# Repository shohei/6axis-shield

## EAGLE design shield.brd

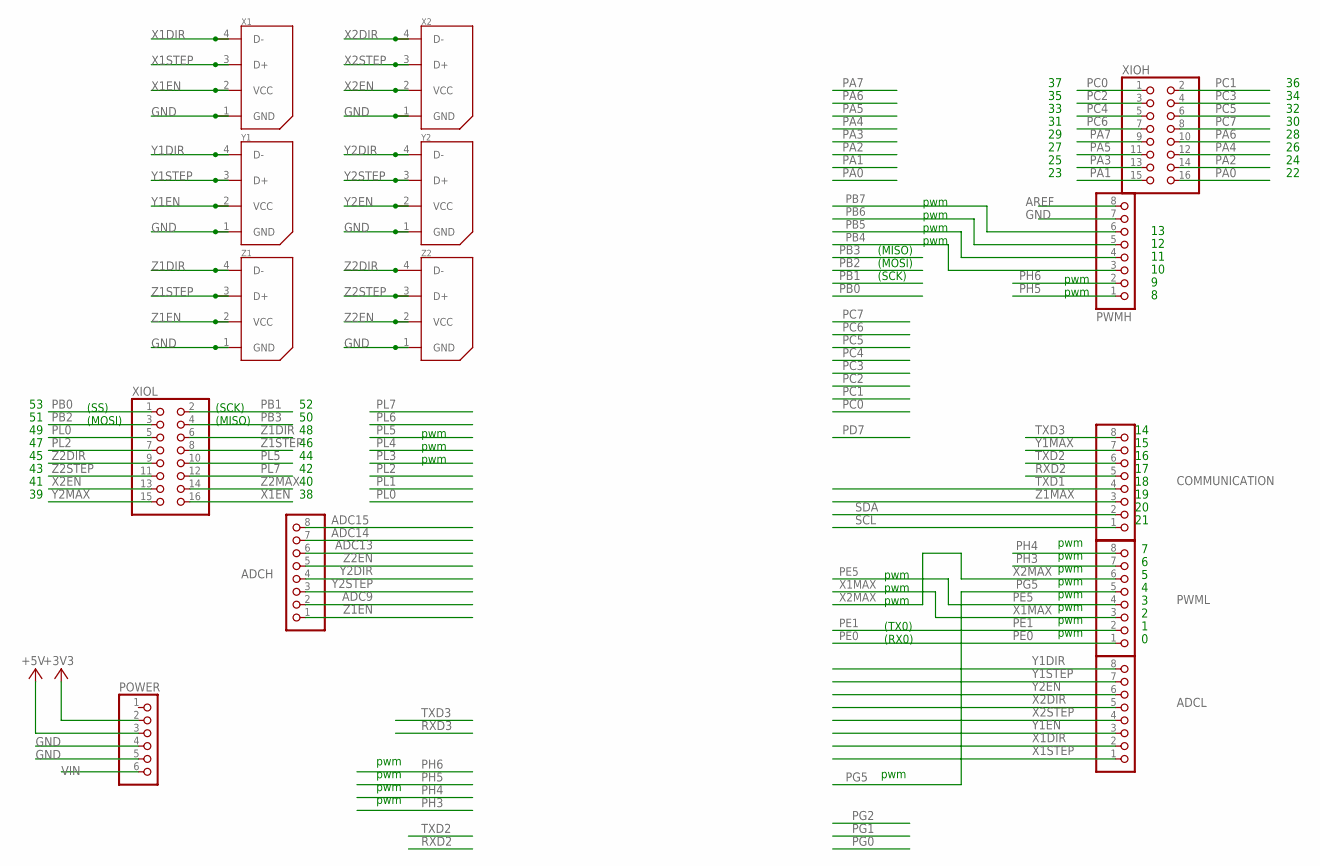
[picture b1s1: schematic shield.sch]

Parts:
ADCH: PINHD-1X8; 1X08
ADCL: PINHD-1X8; 1X08
COMMUNICATION: PINHD-1X8; 1X08
POWER: PINHD-1X6; 1X06
PWMH: PINHD-1X8; 1X08
PWML: PINHD-1X8; 1X08
X1, X2: 22-03-5045; 5267-4
XIOH: PINHD-2X8; 2X08
XIOL: PINHD-2X8; 2X08
Y1, Y2: 22-03-5045; 5267-4
Z1, Z2: 22-03-5045; 5267-4

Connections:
+3V3: POWER.2
+5V: POWER.3
ADC9: ADCH.2
ADC13: ADCH.6
ADC14: ADCH.7
ADC15: ADCH.8
AREF: PWMH.8
GND: POWER.4, POWER.5, PWMH.7, X1.1 (GND), X2.1 (GND), Y1.1 (GND), Y2.1 (GND), Z1.1 (GND), Z2.1 (GND)
PA0: XIOH.16
PA1: XIOH.15
PA2: XIOH.14
PA3: XIOH.13
PA4: XIOH.12
PA5: XIOH.11
PA6: XIOH.10
PA7: XIOH.9
PB0: XIOL.1
PB1: XIOL.2
PB2: XIOL.3
PB3: XIOL.4
PB4: PWMH.3
PB5: PWMH.4
PB6: PWMH.5
PB7: PWMH.6
PC0: XIOH.1
PC1: XIOH.2
PC2: XIOH.3
PC3: XIOH.4
PC4: XIOH.5
PC5: XIOH.6
PC6: XIOH.7
PC7: XIOH.8
PE0: PWML.1
PE1: PWML.2
PE5: PWML.4
PG5: PWML.5
PH3: PWML.7
PH4: PWML.8
PH5: PWMH.1
PH6: PWMH.2
PL0: XIOL.5
PL2: XIOL.7
PL5: XIOL.10
PL7: XIOL.12
RXD2: COMMUNICATION.5
SCL: COMMUNICATION.1
SDA: COMMUNICATION.2
TXD1: COMMUNICATION.4
TXD2: COMMUNICATION.6
TXD3: COMMUNICATION.8
VIN: POWER.6
X1DIR: ADCL.2, X1.4 (D-)
X1EN: X1.2 (VCC), XIOL.16
X1MAX: PWML.3
X1STEP: ADCL.1, X1.3 (D+)
X2DIR: ADCL.5, X2.4 (D-)
X2EN: X2.2 (VCC), XIOL.13
X2MAX: PWML.6
X2STEP: ADCL.4, X2.3 (D+)
Y1DIR: ADCL.8, Y1.4 (D-)
Y1EN: ADCL.3, Y1.2 (VCC)
Y1MAX: COMMUNICATION.7
Y1STEP: ADCL.7, Y1.3 (D+)
Y2DIR: ADCH.4, Y2.4 (D-)
Y2EN: ADCL.6, Y2.2 (VCC)
Y2MAX: XIOL.15
Y2STEP: ADCH.3, Y2.3 (D+)
Z1DIR: XIOL.6, Z1.4 (D-)
Z1EN: ADCH.1, Z1.2 (VCC)
Z1MAX: COMMUNICATION.3
Z1STEP: XIOL.8, Z1.3 (D+)
Z2DIR: XIOL.9, Z2.4 (D-)
Z2EN: ADCH.5, Z2.2 (VCC)
Z2MAX: XIOL.14
Z2STEP: XIOL.11, Z2.3 (D+)

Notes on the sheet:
pwm
(TX0)
(RX0)
(MISO)
(SCK)
(MOSI)
(SS)

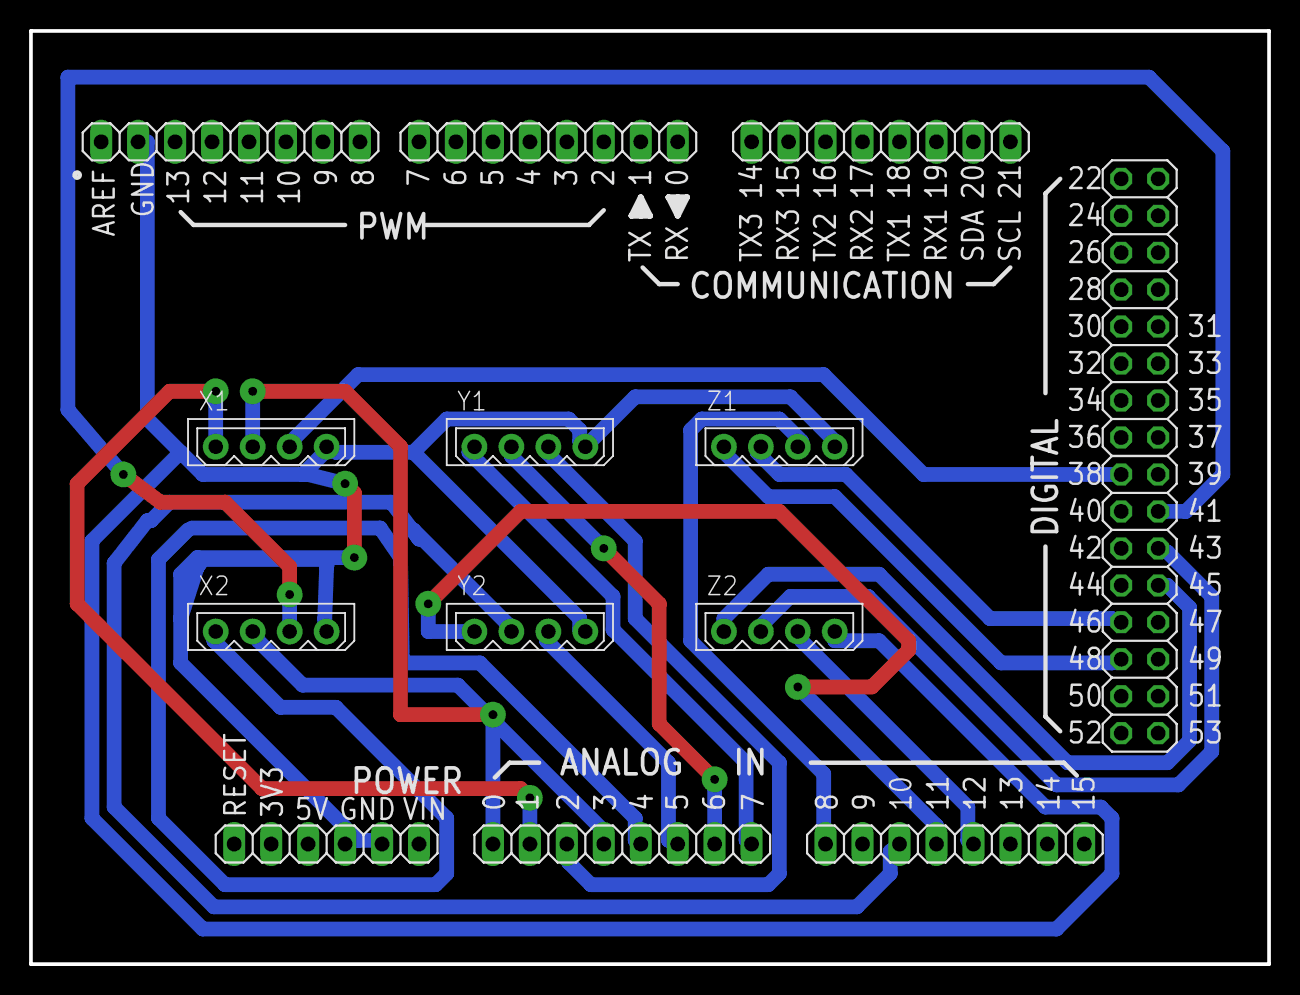
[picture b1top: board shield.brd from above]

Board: 2 copper layers, 85.1 x 64.1 mm, 14 parts (0 on the bottom side), 19 nets.

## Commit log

2016-04-21 change to 4 pin header
